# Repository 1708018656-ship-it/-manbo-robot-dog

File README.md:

# 曼波机器狗（Manbo Robot Dog）

> 基于 STM32F103C8T6 的低成本桌面四足机器狗：**说口令就走，还会回话、做表情**。精简版整机约 50–75 元（4 个 SG90 舵机 + SU-03T 离线语音 + OLED + 4 节 5 号电池）；完整版另有蓝牙、超声波避障、红外防跌落、电池检测。

**维护者：[@1708018656-ship-it](https://github.com/1708018656-ship-it)** · 基于 [RussellCooper-DJZ/manbo-robot-dog](https://github.com/RussellCooper-DJZ/manbo-robot-dog)（MIT）

本仓库是在原项目基础上的**整体优化版**：修了一批真实 bug，固件全面非阻塞化，新增看门狗、电池检测和舵机校准，并从零设计了一块可直接下单的**扩展底板 V2**。逐条改动见 [OPTIMIZATION_PLAN.md](OPTIMIZATION_PLAN.md)。

## 两种版本

| | 精简版（推荐入门，省钱） | 完整版 |
|---|---|---|
| 功能 | 语音口令控制 + 运动 + 语音回复 + OLED 表情 | 以上全部 + 蓝牙 + 超声波避障 + 红外防跌落 + 电池检测 |
| 硬件 | [hardware/lite/](hardware/lite/README.md)：70×54 mm 小板，4 节 5 号电池，SU-03T 语音模块（自带喇叭回话），OLED | [hardware/](hardware/README.md)：100×90 mm 扩展底板 V2，2S 锂电 |
| 固件 | `make LITE=1` | `make V2=1`（或原版飞线 `make`） |
| 大概成本（不含电池、下载器） | 约 50–75 元 | 明显更高（多了语音合成、蓝牙、屏幕、传感器和锂电供电） |

<p align="center"><br><sub>精简版底板（70 × 54 mm，13 个元件）。完整版底板见 <a href="hardware/README.md">hardware/</a></sub></p>

## 这一版改了什么

**修复的 bug（都有对应测试或验证）**
- 超声波避障基本测不到 170 cm 内的障碍物（10 ms 轮询漏掉短回波）→ 直接读中断累计的回波宽度
- 主循环命令分发顺序错误，非阻塞状态机被绕过、每个动作执行两遍
- 高级动作语音变成念拼音字母；长语音被截断且会切坏半个汉字
- 体力为 0 时命令被重放；体力 / 开心值只显示 2 位；语音模块与主控命令编码不一致
- `Time` 变量 volatile 不一致、`speed==0` 除零、`commands.h` 缺头文件、ASR `__dso_handle` 重复定义

**固件改进**
- 主循环里不再有秒级延时：动作、语音、状态播报、红外防跌落、OLED 刷新全部非阻塞
- 独立看门狗（约 1.6 s），急停在任何时候都能立即响应
- 电池电压检测（V2 底板）：低电提醒、过低自动趴下
- 每个舵机可单独微调角度（`Hardware/ServoMath.h` 里的 `SERVO_TRIM_DEG`）
- 全部源码 UTF-8（转换前后二进制逐字节一致），GBK 语音文本用 `\x` 转义
- 新增 GCC 构建（`make`），Keil 工程照常可用；删除死代码后代码段约 22.5 KB / 64 KB

**硬件**：见 [hardware/README.md](hardware/README.md)——双降压分离舵机 / 逻辑供电、防反接、自恢复保险丝、超声波 Echo 分压、红外改到耐 5 V 引脚。

## 快速开始

### 1. 编译固件

| 方式 | 命令 / 操作 |
|---|---|
| Keil MDK 5 | 打开 `Project.uvprojx` 编译。用 V2 底板时在 Options → C/C++ → Define 加 `MANBO_BOARD_V2` |
| GCC | `sudo apt install gcc-arm-none-eabi` 后 `make`（原版接线）、`make V2=1`（V2 底板）或 `make LITE=1`（精简版），产物在 `build/` |
| 烧录 | ST-Link：`make flash`，或 Keil / STM32CubeProgrammer 烧 `build/manbo.hex` |

GitHub Actions 每次推送都会编出三种版本的 `.hex`，可在 Actions 页面直接下载。

### 2. 接线

- **用 V2 底板**：模块直接插，见 [hardware/kicad/pinmap.md](hardware/kicad/pinmap.md)
- **原版飞线**：

| 功能 | 引脚 |
|---|---|
| 舵机 1–4（TIM3 CH1–4） | PA6、PA7、PB0、PB1 |
| 蓝牙 HC-05（USART1） | PA9 → 模块 RXD，PA10 ← 模块 TXD |
| SYN6288（USART2） | PA2 → 模块 RXD，PA3 ← 模块 TXD |
| 语音识别（USART3） | PB10 → 模块 RXD，PB11 ← 模块 TXD |
| OLED（软件 I2C） | PB8 SCL，PB9 SDA |
| HC-SR04 | PA0 Trig，PA1 Echo（**建议加 1k/2k 分压，PA1 不耐 5 V**） |
| 红外 ×4 | 前 PA11、后 PA4、左 PA12、右 PA5（V2：PB12–PB15） |

舵机必须单独供电（5 V ≥ 3 A），不要从 Blue Pill 取电。

### 3. 控制

蓝牙串口助手发单个字符即可，9600 8N1。常用：`f` 前进、`b` 后退、`l`/`r` 转弯、`5` 急停、`d` 跳舞、`o` 打招呼、`p` 趴下睡觉、`Z` 播报状态、`x`/`c` 开关超声波避障、`H`/`h` 开关红外防跌落。完整表格（含体力 / 开心值规则）见 [docs/protocol.md](docs/protocol.md)。

## 仓库结构

```text
User/        应用层：main 主循环、ActionTask 动作状态机、AudioTask 语音、SensorTask 超声波、
             BatteryTask 电池、PetStats 体力/开心值、BoardConfig 板型引脚、Watchdog
Hardware/    驱动：Servo/ServoMath、PWM、OLED、syn6288、Hongwai 红外、UltrasonicWave、Timer
System/      Timebase 1 ms 时基、usart1–3（环形缓冲）、Delay、GbkText
Library/ Start/   ST 标准外设库与 CMSIS（Keil 启动文件）
gcc/         GCC 链接脚本与启动文件；Makefile 在根目录
ASRPro_Code/ ESP32 + ASR PRO 语音识别子项目（PlatformIO）
hardware/    扩展底板 V2：生成脚本、KiCad 工程、BOM、Gerber
tests/host/  主机单元测试（无需开发板）：bash tests/host/run_tests.sh
tools/       编码转换、Cortex-M3 语法检查等脚本
docs/        协议、设计方案、审查报告
```

## 测试

```bash
bash tests/host/run_tests.sh          # 状态机、协议覆盖、GBK 截断、体力规则、电池、超声波、舵机换算
bash tools/check_firmware_syntax.sh   # 用 clang 对 Keil 工程全部 C 文件做 Cortex-M3 检查
python3 hardware/gen/build.py --check # 重新生成底板并跑 ERC/DRC，确认提交的文件是最新的
# CI 另外用 KiCad 8 的 kicad-cli 做官方 ERC/DRC
```

## 文档

| 文档 | 说明 |
|---|---|
| [docs/protocol.md](docs/protocol.md) | 串口命令协议（STM32 与语音模块共用的唯一权威表） |
| [hardware/lite/README.md](hardware/lite/README.md) | **精简版**：底板、供电、组装 |
| [docs/su03t.md](docs/su03t.md) | 精简版 SU-03T 口令配置表 |
| [hardware/README.md](hardware/README.md) | 完整版扩展底板：下单、焊接、上电检查 |
| [hardware/采购清单.md](hardware/采购清单.md) | 整机采购清单（板子、模块、舵机、电池） |
| [OPTIMIZATION_PLAN.md](OPTIMIZATION_PLAN.md) | 本次优化的全部改动与原因 |
| [docs/non_blocking_state_machine.md](docs/non_blocking_state_machine.md) | 非阻塞状态机设计 |
| [ASRPro_Code/README.md](ASRPro_Code/README.md) | 语音识别子项目 |

`docs/` 里 `hardware.md`、`hardware-interface.md`、`gait-control.md`、`software.md`、`code_examples.md` 和两篇论文是早期资料，描述的是 8/12 舵机或 STM32F407 的扩展设想，**与当前代码不一致**，仅供参考。

## 已知限制

- 固件改动已通过主机测试和 Cortex-M3 编译检查，**尚未在实物上回归测试**；如发现动作异常，可用 `git log` 定位并反馈。
- V2 底板是脚本生成并自动布线的，已过 KiCad 8 官方 ERC/DRC，**尚未打样**。
- 4 舵机每条腿只有 1 个自由度，步态以趣味动作为主，不追求真实四足运动学。

## 许可证与致谢

MIT 许可证，见 [LICENSE](LICENSE)。原始项目作者 RussellCooper-DJZ；本版由 [@1708018656-ship-it](https://github.com/1708018656-ship-it) 维护和优化，保留原作者版权声明。

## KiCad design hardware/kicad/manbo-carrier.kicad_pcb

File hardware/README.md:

# 曼波机器狗扩展底板 V2

原项目只有飞线接法，没有任何原理图和 PCB。这块底板把 Blue Pill（STM32F103C8T6）、4 个舵机、所有模块和电源集成到一块 100 × 90 mm 的双层板上，同时解决了原接法的几个硬件问题。

> ⚠️ 这块板是用脚本生成并自动布线的，已通过脚本自带的 ERC/DRC，以及 **KiCad 8 官方 ERC/DRC（0 违规、0 未连接，CI 每次推送自动跑）**，**但还没有打样、焊接或实测过**。第一次打样建议先少量（5 片），按下面的「上电检查」一步一步来。

## 和原版接线相比修了什么

| 问题 | 原接法 | V2 底板 |
|---|---|---|
| 舵机一起动 MCU 就复位 | 舵机和逻辑共用一路 5 V | 舵机和逻辑**各用一个降压模块**，舵机轨加 1000 µF |
| HC-SR04 Echo 5 V 接 PA1 | PA1 **不耐 5 V**，长期可能损坏芯片 | 1k/2k 分压到 3.33 V |
| 红外占用 PA11/PA12 | 这是 USB D-/D+，Blue Pill 板载上拉会干扰读数 | 改到 PB12–PB15（耐 5 V） |
| 没有电池电压检测 | ADC 引脚全被占用 | VBAT 经 100k/33k 分压接 PA4，低电提醒 + 自动趴下 |
| 电池接反直接烧 | 无保护 | Q2 P-MOS 防反接 + 3 A 自恢复保险丝 |
| 开关承受全部电流 | 小拨动开关只能过 0.5 A | 开关只控制 Q1 栅极，大电流走 MOS 管 |

## 文件

| 路径 | 内容 |
|---|---|
| `fab/manbo-carrier-gerbers.zip` | **直接上传到嘉立创/JLCPCB 等下单** |
| `kicad/manbo-carrier.kicad_pro` | KiCad 8 工程（原理图 + PCB，可继续修改） |
| `kicad/bom.csv` | 板上元件清单（位号、封装，自动生成） |
| `采购清单.md` | **整机采购清单**（含舵机、模块、电池等） |
| `kicad/pinmap.md` | Blue Pill 每个引脚接到哪里 |
| `kicad/schematic-preview.svg` | 原理图预览（手机也能看） |
| `kicad/drc-report.txt` | 布线和 DRC 结果 |
| `gen/` | 生成脚本：**改设计请改 `gen/design.py` / `gen/layout.py`**，然后运行 `python3 hardware/gen/build.py` |

## 下单参数

层数 2，板厚 1.6 mm，尺寸 100 × 90 mm，最小线宽 0.254 mm（10 mil）、最小间距 0.2 mm，过孔 0.5 mm 孔 / 1.0 mm 焊盘，铜厚 1 oz，阻焊颜色随意。这些都在嘉立创 EDA 的默认规则以内，导入后 DRC 不需要改规则。这些都是常规工艺，打样通常最便宜那档就够。

## 焊接顺序

1. 贴片：Q1、Q2（SOIC-8，注意 1 脚圆点）、F1、电阻电容、LED（绿点/竖线 = 负极，对应丝印 1 脚）
2. 直插：排针/排母、XH 座、电解电容（**长脚 = 正极 = 方焊盘**）
3. Blue Pill 用两条 1×20 **排母**插装，方便更换
4. 降压模块：用排针立在板上，或用短线接到 IN+/IN-/OUT+/OUT- 四个大孔

## 上电检查（第一次一定要按顺序）

1. **先不插 Blue Pill、不接舵机和模块。**
2. 接电池（或 7–8 V 限流电源，限流 0.5 A），J15 接上开关并打开，电源灯亮。
3. **把两个降压模块都调到 5.0 V 再往下走**——MP1584 这类可调模块出厂电压是随机的，直接接可能把 Blue Pill 和舵机烧掉。
4. 用万用表确认：`+5V_SERVO` 和 `+5V` 都是 5.0 V，Blue Pill 排母的 3V3 脚此时为 0（Blue Pill 没插）。
5. 关电，插上 Blue Pill，开电：3V3 脚应为 3.3 V。
6. 烧录 **V2 固件**：`make V2=1`，或在 Keil 里 Options → C/C++ → Define 加上 `MANBO_BOARD_V2`。原版固件引脚不同，红外和电池检测会不工作。
7. 再依次接 OLED、舵机、蓝牙等模块。

## 注意

- **Blue Pill 的 USB 口和电池不要同时供电**：Blue Pill 的 USB 5 V 和 5V 引脚之间多数没有二极管，会互相倒灌。烧录用 SWD（ST-Link）最方便。
- OLED 有两种引脚顺序（GND-VCC 和 VCC-GND），插之前看一眼模块丝印。
- HC-05 是 6 针，HC-06 是 4 针（插在 J6 的 2–5 脚）。模块方向以丝印 `VCC GND TXD RXD` 为准。
- SYN6288 和 ASR PRO 模块的引脚顺序各家不一样，用杜邦线按丝印 `VCC GND RXD TXD` 接（RXD/TXD 是模块自己的引脚名）。
- GND 铺铜：Gerber 里已经带了铺铜。在 KiCad 里打开 PCB 后，如果要改板，先按 **B**（填充全部覆铜）再出图。
- 引脚表以常见 Blue Pill 为准（左排 PB12…3V3，右排 GND…VBAT）。个别山寨板丝印不同，焊之前用 `kicad/pinmap.md` 对照一下。

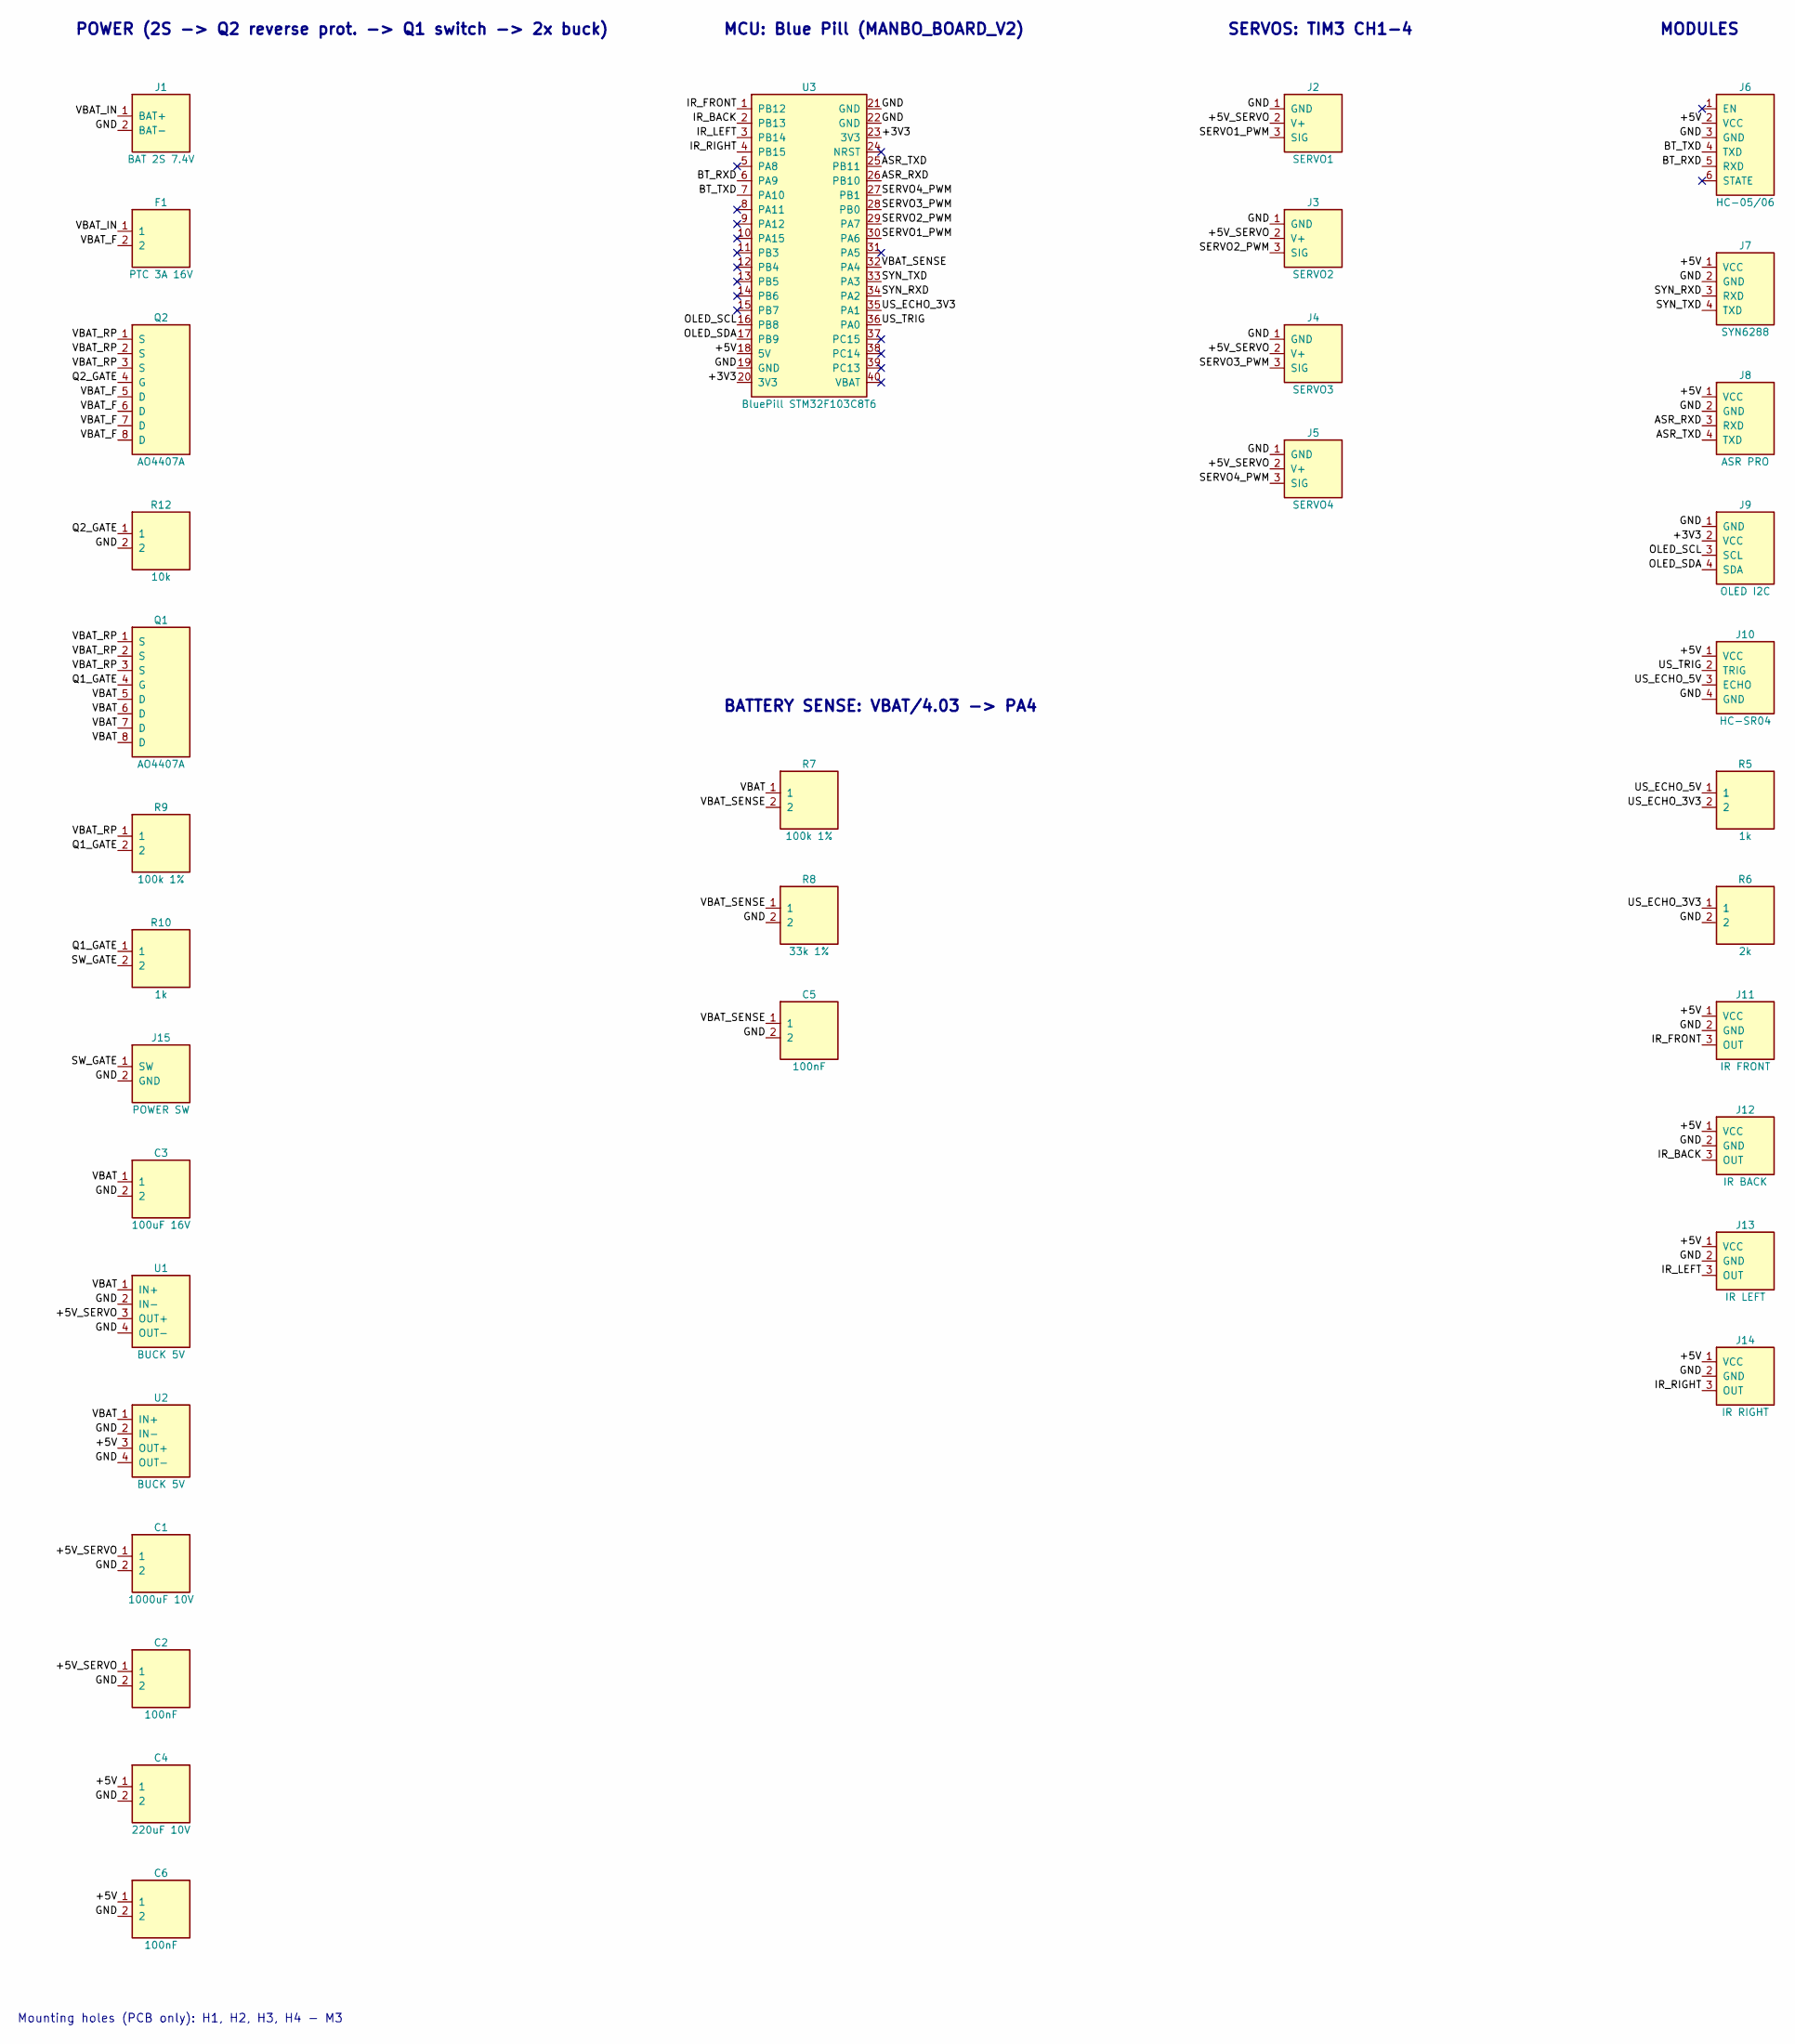
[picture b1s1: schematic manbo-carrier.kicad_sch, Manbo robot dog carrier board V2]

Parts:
C1: 1000uF 10V; CP_Radial_D10.0mm_P5.00mm; LCSC 1000uF 10V 10x13
C2, C5, C6: 100nF; C_0805_2012Metric; LCSC 0805 100nF
C3: 100uF 16V; CP_Radial_D6.3mm_P2.50mm; LCSC 100uF 16V 6.3x7
C4: 220uF 10V; CP_Radial_D6.3mm_P2.50mm; LCSC 220uF 10V 6.3x7
F1: PTC 3A 16V; Fuse_2920_7451Metric; LCSC SMD2920P300TF/24
J1: BAT 2S 7.4V; JST_XH_B2B-XH-A_1x02_P2.50mm_Vertical; LCSC XH2.54 2P
J2: SERVO1; PinHeader_1x03_P2.54mm_Vertical; LCSC 2.54mm header 3P
J3: SERVO2; PinHeader_1x03_P2.54mm_Vertical; LCSC 2.54mm header 3P
J4: SERVO3; PinHeader_1x03_P2.54mm_Vertical; LCSC 2.54mm header 3P
J5: SERVO4; PinHeader_1x03_P2.54mm_Vertical; LCSC 2.54mm header 3P
J6: HC-05/06; PinHeader_1x06_P2.54mm_Vertical; LCSC 2.54mm header 6P
J7: SYN6288; PinHeader_1x04_P2.54mm_Vertical; LCSC 2.54mm header 4P
J8: ASR PRO; PinHeader_1x04_P2.54mm_Vertical; LCSC 2.54mm header 4P
J9: OLED I2C; PinHeader_1x04_P2.54mm_Vertical; LCSC 2.54mm header 4P
J10: HC-SR04; PinHeader_1x04_P2.54mm_Vertical; LCSC 2.54mm header 4P
J11: IR FRONT; PinHeader_1x03_P2.54mm_Vertical; LCSC 2.54mm header 3P
J12: IR BACK; PinHeader_1x03_P2.54mm_Vertical; LCSC 2.54mm header 3P
J13: IR LEFT; PinHeader_1x03_P2.54mm_Vertical; LCSC 2.54mm header 3P
J14: IR RIGHT; PinHeader_1x03_P2.54mm_Vertical; LCSC 2.54mm header 3P
J15: POWER SW; JST_XH_B2B-XH-A_1x02_P2.50mm_Vertical; LCSC XH2.54 2P
Q1, Q2: AO4407A; SOIC-8_3.9x4.9mm_P1.27mm; LCSC AO4407A
R5, R10: 1k; R_0805_2012Metric; LCSC 0805 1k
R6: 2k; R_0805_2012Metric; LCSC 0805 2k
R7, R9: 100k 1%; R_0805_2012Metric; LCSC 0805 100k 1%
R8: 33k 1%; R_0805_2012Metric; LCSC 0805 33k 1%
R12: 10k; R_0805_2012Metric; LCSC 0805 10k
U1, U2: BUCK 5V; BuckModule_2x2_P2.54mm_17.78mm; LCSC MP1584 / Mini560 module
U3: BluePill STM32F103C8T6; BluePill_Socket_2x20_W15.24mm; LCSC Blue Pill STM32F103C8T6

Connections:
+3V3: J9.2 (VCC), U3.20 (3V3), U3.23 (3V3)
+5V: C4.1, C6.1, J6.2 (VCC), J7.1 (VCC), J8.1 (VCC), J10.1 (VCC), J11.1 (VCC), J12.1 (VCC), J13.1 (VCC), J14.1 (VCC), U2.3 (OUT+), U3.18 (5V)
+5V_SERVO: C1.1, C2.1, J2.2 (V+), J3.2 (V+), J4.2 (V+), J5.2 (V+), U1.3 (OUT+)
ASR_RXD: J8.3 (RXD), U3.26 (PB10)
ASR_TXD: J8.4 (TXD), U3.25 (PB11)
BT_RXD: J6.5 (RXD), U3.6 (PA9)
BT_TXD: J6.4 (TXD), U3.7 (PA10)
GND: C1.2, C2.2, C3.2, C4.2, C5.2, C6.2, J1.2 (BAT-), J2.1 (GND), J3.1 (GND), J4.1 (GND), J5.1 (GND), J6.3 (GND), J7.2 (GND), J8.2 (GND), J9.1 (GND), J10.4 (GND), J11.2 (GND), J12.2 (GND), J13.2 (GND), J14.2 (GND), J15.2 (GND), R6.2, R8.2, R12.2, U1.2 (IN-), U1.4 (OUT-), U2.2 (IN-), U2.4 (OUT-), U3.19 (GND), U3.21 (GND), U3.22 (GND)
IR_BACK: J12.3 (OUT), U3.2 (PB13)
IR_FRONT: J11.3 (OUT), U3.1 (PB12)
IR_LEFT: J13.3 (OUT), U3.3 (PB14)
IR_RIGHT: J14.3 (OUT), U3.4 (PB15)
OLED_SCL: J9.3 (SCL), U3.16 (PB8)
OLED_SDA: J9.4 (SDA), U3.17 (PB9)
Q1_GATE: Q1.4 (G), R9.2, R10.1
Q2_GATE: Q2.4 (G), R12.1
SERVO1_PWM: J2.3 (SIG), U3.30 (PA6)
SERVO2_PWM: J3.3 (SIG), U3.29 (PA7)
SERVO3_PWM: J4.3 (SIG), U3.28 (PB0)
SERVO4_PWM: J5.3 (SIG), U3.27 (PB1)
SW_GATE: J15.1 (SW), R10.2
SYN_RXD: J7.3 (RXD), U3.34 (PA2)
SYN_TXD: J7.4 (TXD), U3.33 (PA3)
US_ECHO_3V3: R5.2, R6.1, U3.35 (PA1)
US_ECHO_5V: J10.3 (ECHO), R5.1
US_TRIG: J10.2 (TRIG), U3.36 (PA0)
VBAT: C3.1, Q1.5 (D), Q1.6 (D), Q1.7 (D), Q1.8 (D), R7.1, U1.1 (IN+), U2.1 (IN+)
VBAT_F: F1.2, Q2.5 (D), Q2.6 (D), Q2.7 (D), Q2.8 (D)
VBAT_IN: F1.1, J1.1 (BAT+)
VBAT_RP: Q1.1 (S), Q1.2 (S), Q1.3 (S), Q2.1 (S), Q2.2 (S), Q2.3 (S), R9.1
VBAT_SENSE: C5.1, R7.2, R8.1, U3.32 (PA4)

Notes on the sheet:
POWER (2S -> Q2 reverse prot. -> Q1 switch -> 2x buck)
MCU: Blue Pill (MANBO_BOARD_V2)
SERVOS: TIM3 CH1-4
MODULES
BATTERY SENSE: VBAT/4.03 -> PA4
Mounting holes (PCB only): H1, H2, H3, H4 - M3

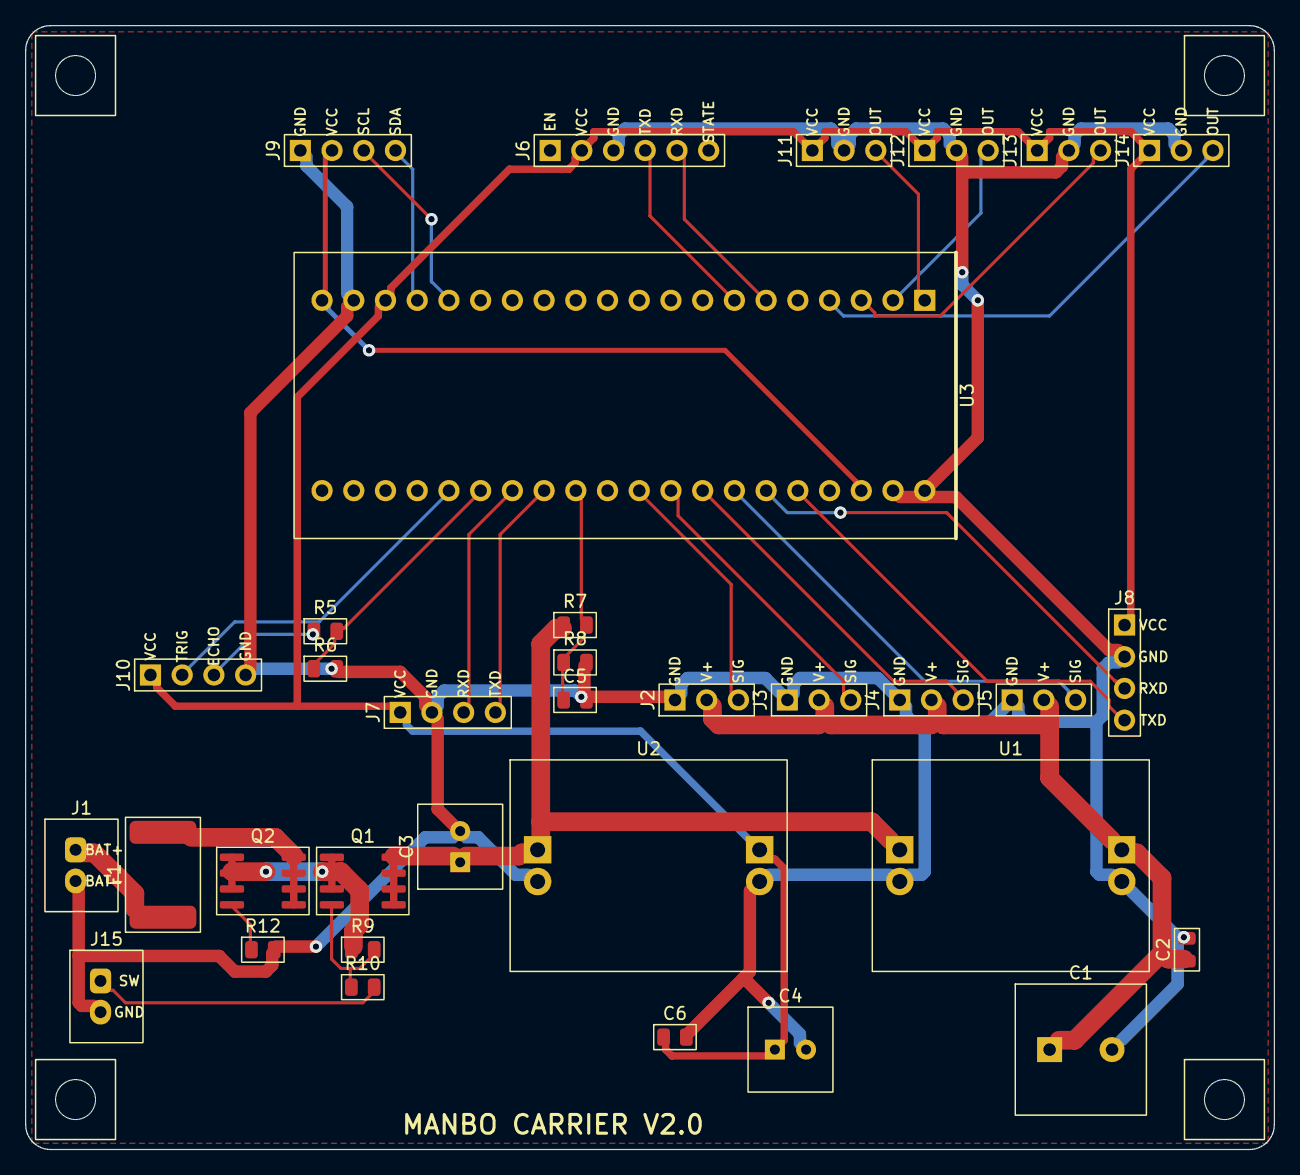
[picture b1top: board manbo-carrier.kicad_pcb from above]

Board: 2 copper layers, 100.0 x 90.0 mm, 38 parts (0 on the bottom side), 31 nets.

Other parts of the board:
H1, H2, H3, H4: M3; MountingHole_3.2mm_M3

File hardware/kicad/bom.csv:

Qty,References,Value,Footprint,Search keyword (LCSC/Taobao),Notes
1,C1,1000uF 10V,CP_Radial_D10.0mm_P5.00mm,1000uF 10V 10x13,
3,C2 C5 C6,100nF,C_0805_2012Metric,0805 100nF,
1,C3,100uF 16V,CP_Radial_D6.3mm_P2.50mm,100uF 16V 6.3x7,
1,C4,220uF 10V,CP_Radial_D6.3mm_P2.50mm,220uF 10V 6.3x7,
1,F1,PTC 3A 16V,Fuse_2920_7451Metric,SMD2920P300TF/24,"Resettable fuse, 3 A hold, >=16 V (servo stall protection)"
4,H1 H2 H3 H4,M3,MountingHole_3.2mm_M3,,M3 mounting hole
1,J1,BAT 2S 7.4V,JST_XH_B2B-XH-A_1x02_P2.50mm_Vertical,XH2.54 2P,2S Li-ion/LiPo input (6.4-8.4 V)
1,J2,SERVO1,PinHeader_1x03_P2.54mm_Vertical,2.54mm header 3P,"SG90 servo 1 (brown=GND, red=V+, orange=SIG)"
1,J3,SERVO2,PinHeader_1x03_P2.54mm_Vertical,2.54mm header 3P,"SG90 servo 2 (brown=GND, red=V+, orange=SIG)"
1,J4,SERVO3,PinHeader_1x03_P2.54mm_Vertical,2.54mm header 3P,"SG90 servo 3 (brown=GND, red=V+, orange=SIG)"
1,J5,SERVO4,PinHeader_1x03_P2.54mm_Vertical,2.54mm header 3P,"SG90 servo 4 (brown=GND, red=V+, orange=SIG)"
1,J6,HC-05/06,PinHeader_1x06_P2.54mm_Vertical,2.54mm header 6P,Bluetooth module socket (HC-05 6-pin; HC-06 4-pin plugs into pins 2-5)
1,J7,SYN6288,PinHeader_1x04_P2.54mm_Vertical,2.54mm header 4P,SYN6288 speech synthesis module
1,J8,ASR PRO,PinHeader_1x04_P2.54mm_Vertical,2.54mm header 4P,ASR PRO voice recognition module
1,J9,OLED I2C,PinHeader_1x04_P2.54mm_Vertical,2.54mm header 4P,0.96in SSD1306 I2C OLED (plugs in directly)
1,J10,HC-SR04,PinHeader_1x04_P2.54mm_Vertical,2.54mm header 4P,Ultrasonic sensor (plugs in directly)
1,J11,IR FRONT,PinHeader_1x03_P2.54mm_Vertical,2.54mm header 3P,"IR cliff sensor front (FC-51 style, VCC GND OUT)"
1,J12,IR BACK,PinHeader_1x03_P2.54mm_Vertical,2.54mm header 3P,"IR cliff sensor back (FC-51 style, VCC GND OUT)"
1,J13,IR LEFT,PinHeader_1x03_P2.54mm_Vertical,2.54mm header 3P,"IR cliff sensor left (FC-51 style, VCC GND OUT)"
1,J14,IR RIGHT,PinHeader_1x03_P2.54mm_Vertical,2.54mm header 3P,"IR cliff sensor right (FC-51 style, VCC GND OUT)"
1,J15,POWER SW,JST_XH_B2B-XH-A_1x02_P2.50mm_Vertical,XH2.54 2P,"External ON/OFF switch (signal level, any small switch)"
1,Q1,AO4407A,SOIC-8_3.9x4.9mm_P1.27mm,AO4407A,"P-MOSFET -30V -12A, power switch"
1,Q2,AO4407A,SOIC-8_3.9x4.9mm_P1.27mm,AO4407A,"P-MOSFET -30V -12A, reverse-polarity protection"
1,R6,2k,R_0805_2012Metric,0805 2k,
1,R8,33k 1%,R_0805_2012Metric,0805 33k 1%,
2,R7 R9,100k 1%,R_0805_2012Metric,0805 100k 1%,
2,R5 R10,1k,R_0805_2012Metric,0805 1k,
1,R12,10k,R_0805_2012Metric,0805 10k,
1,U1,BUCK 5V,BuckModule_2x2_P2.54mm_17.78mm,MP1584 / Mini560 module,"DC-DC buck module, servo rail, >=3 A (e.g. Mini560 5V / MP1584)"
1,U2,BUCK 5V,BuckModule_2x2_P2.54mm_17.78mm,MP1584 / Mini560 module,"DC-DC buck module, logic rail, >=1 A (e.g. MP1584 / Mini360 set to 5.0 V)"
1,U3,BluePill STM32F103C8T6,BluePill_Socket_2x20_W15.24mm,Blue Pill STM32F103C8T6,Blue Pill on 2x 1x20 female headers

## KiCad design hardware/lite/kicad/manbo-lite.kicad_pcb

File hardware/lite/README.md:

# 曼波机器狗 精简版（LITE）

**听懂口令、走起来、开口回话、屏幕做表情**。语音合成模块、蓝牙、超声波、红外、电池检测全部去掉，换成最便宜的方案。

## 和完整版的区别

| | 完整版 V2 | 精简版 |
|---|---|---|
| 控制 | 蓝牙 + 语音识别（ASR PRO） | **语音口令（SU-03T）** |
| 语音回复 | SYN6288（约 50 元） | **SU-03T 自带喇叭**：识别后自动回话，开机/自动停下时由单片机触发播报 |
| 屏幕表情 | 有 | **有**（0.96 寸 OLED，直接插 J7） |
| 超声波 / 红外 / 电池检测 | 有 | 无 |
| 供电 | 2S 锂电 + 平衡充 + 两个降压模块 + MOS 管 | **4 节 5 号电池盒（带开关）** + 两个二极管 |
| 底板 | 100 × 90 mm，34 个元件 | **70 × 54 mm，13 个元件** |
| 固件 | `make` / `make V2=1` | **`make LITE=1`**（Keil 里加 `MANBO_LITE`） |

## 电源为什么这样设计

- **D1 SS34**：防电池接反；同时把新碱性电池的 6.4 V 降到约 6 V，不超过 SG90 的 6 V 上限。
- **D2 M7（1N4007）**：给 Blue Pill 和语音模块单独供电，再降约 0.8 V，让新碱性电池也不超过 SU-03T 的 5.5 V 上限。
- **C2 470 µF**：舵机启动时电池电压会被拉低，D2 + C2 让单片机和语音模块撑过这一下，不会复位。
- **电池**：碱性和镍氢充电电池都能用。镍氢（1.2 V × 4）更耐用；电池快没电时语音模块会先停止响应，这就是该换电池的信号。

## 文件

| 路径 | 内容 |
|---|---|
| `fab/manbo-lite-gerbers.zip` | 直接上传嘉立创下单 |
| `kicad/` | KiCad 8 工程、BOM、引脚表、预览图 |
| [采购清单.md](采购清单.md) | 整机要买的东西 |
| [../../docs/su03t.md](../../docs/su03t.md) | **SU-03T 口令配置表（必看）** |

## 组装和上电

1. 焊 D1、D2（注意二极管有竖线的一端 = 负极，对准丝印竖线）、C3，再焊排针排母、电解电容（长脚正极 = 方焊盘）。
2. **先不插 Blue Pill**，装电池打开开关，量 Blue Pill 排母的 5V 脚：应该在 3.6–5.5 V 之间。
3. 插 Blue Pill，烧录 `make LITE=1` 编出的固件（或 GitHub Actions 里 `manbo-firmware-lite` 的 `.hex`）。
4. 按 [docs/su03t.md](../../docs/su03t.md) 配置好 SU-03T（含「主动播报」三条），插到 J6；OLED 插到 J7（注意 GND-VCC 顺序）；再接舵机。
5. 开机应听到"小呆来啦"、屏幕出现表情。说"小呆小呆，前进"。说"停"立即停；没听清的话 10 秒后会说"走累了"并自己停。

> 不想打板：这块板电路很简单，用一块洞洞板（约 1 元）照着 `kicad/pinmap.md` 飞线也完全可以。

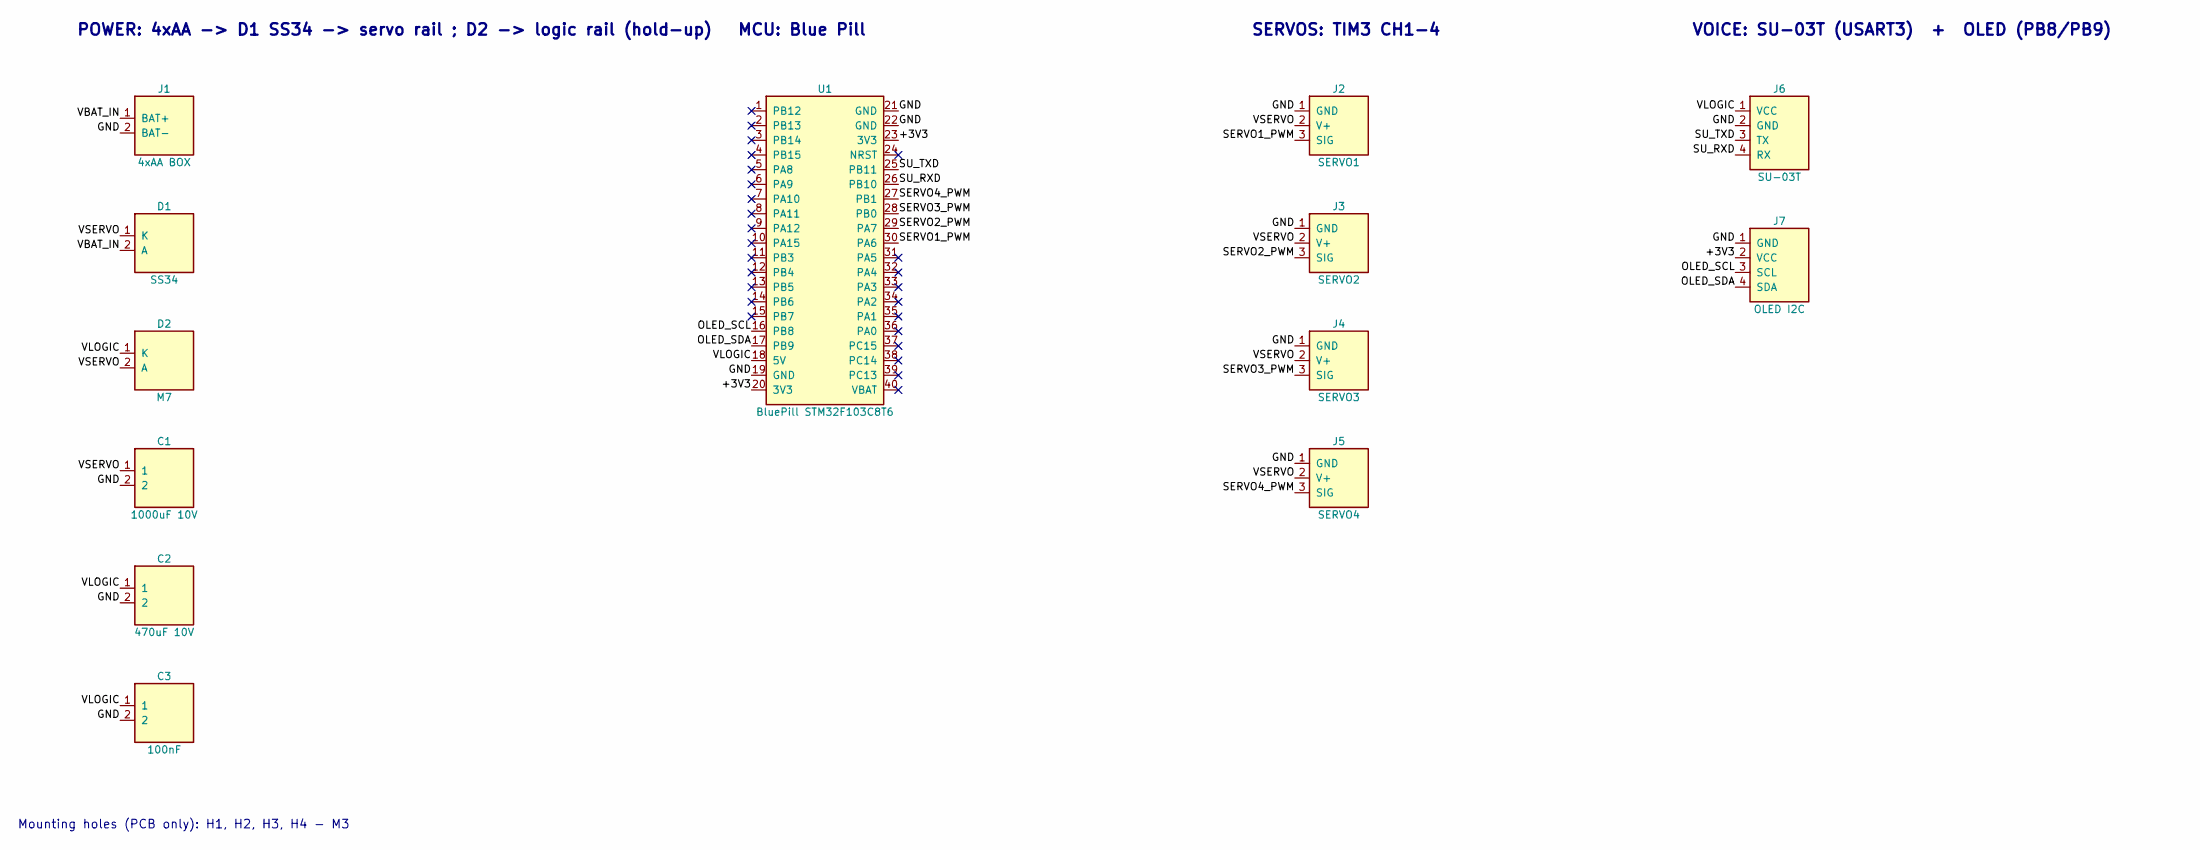
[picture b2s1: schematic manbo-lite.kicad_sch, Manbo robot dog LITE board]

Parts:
C1: 1000uF 10V; CP_Radial_D10.0mm_P5.00mm; LCSC 1000uF 10V 10x13
C2: 470uF 10V; CP_Radial_D8.0mm_P3.50mm; LCSC 470uF 10V 8x12
C3: 100nF; C_0805_2012Metric; LCSC 0805 100nF
D1: SS34; D_SMA; LCSC SS34 SMA
D2: M7; D_SMA; LCSC M7 1N4007 SMA
J1: 4xAA BOX; JST_XH_B2B-XH-A_1x02_P2.50mm_Vertical; LCSC XH2.54 2P
J2: SERVO1; PinHeader_1x03_P2.54mm_Vertical; LCSC 2.54mm header 3P
J3: SERVO2; PinHeader_1x03_P2.54mm_Vertical; LCSC 2.54mm header 3P
J4: SERVO3; PinHeader_1x03_P2.54mm_Vertical; LCSC 2.54mm header 3P
J5: SERVO4; PinHeader_1x03_P2.54mm_Vertical; LCSC 2.54mm header 3P
J6: SU-03T; PinHeader_1x04_P2.54mm_Vertical; LCSC 2.54mm header 4P
J7: OLED I2C; PinHeader_1x04_P2.54mm_Vertical; LCSC 2.54mm header 4P
U1: BluePill STM32F103C8T6; BluePill_Socket_2x20_W15.24mm; LCSC Blue Pill STM32F103C8T6

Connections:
+3V3: J7.2 (VCC), U1.20 (3V3), U1.23 (3V3)
GND: C1.2, C2.2, C3.2, J1.2 (BAT-), J2.1 (GND), J3.1 (GND), J4.1 (GND), J5.1 (GND), J6.2 (GND), J7.1 (GND), U1.19 (GND), U1.21 (GND), U1.22 (GND)
OLED_SCL: J7.3 (SCL), U1.16 (PB8)
OLED_SDA: J7.4 (SDA), U1.17 (PB9)
SERVO1_PWM: J2.3 (SIG), U1.30 (PA6)
SERVO2_PWM: J3.3 (SIG), U1.29 (PA7)
SERVO3_PWM: J4.3 (SIG), U1.28 (PB0)
SERVO4_PWM: J5.3 (SIG), U1.27 (PB1)
SU_RXD: J6.4 (RX), U1.26 (PB10)
SU_TXD: J6.3 (TX), U1.25 (PB11)
VBAT_IN: D1.2 (A), J1.1 (BAT+)
VLOGIC: C2.1, C3.1, D2.1 (K), J6.1 (VCC), U1.18 (5V)
VSERVO: C1.1, D1.1 (K), D2.2 (A), J2.2 (V+), J3.2 (V+), J4.2 (V+), J5.2 (V+)

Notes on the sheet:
POWER: 4xAA -> D1 SS34 -> servo rail ; D2 -> logic rail (hold-up)
MCU: Blue Pill
SERVOS: TIM3 CH1-4
VOICE: SU-03T (USART3) + OLED (PB8/PB9)
Mounting holes (PCB only): H1, H2, H3, H4 - M3

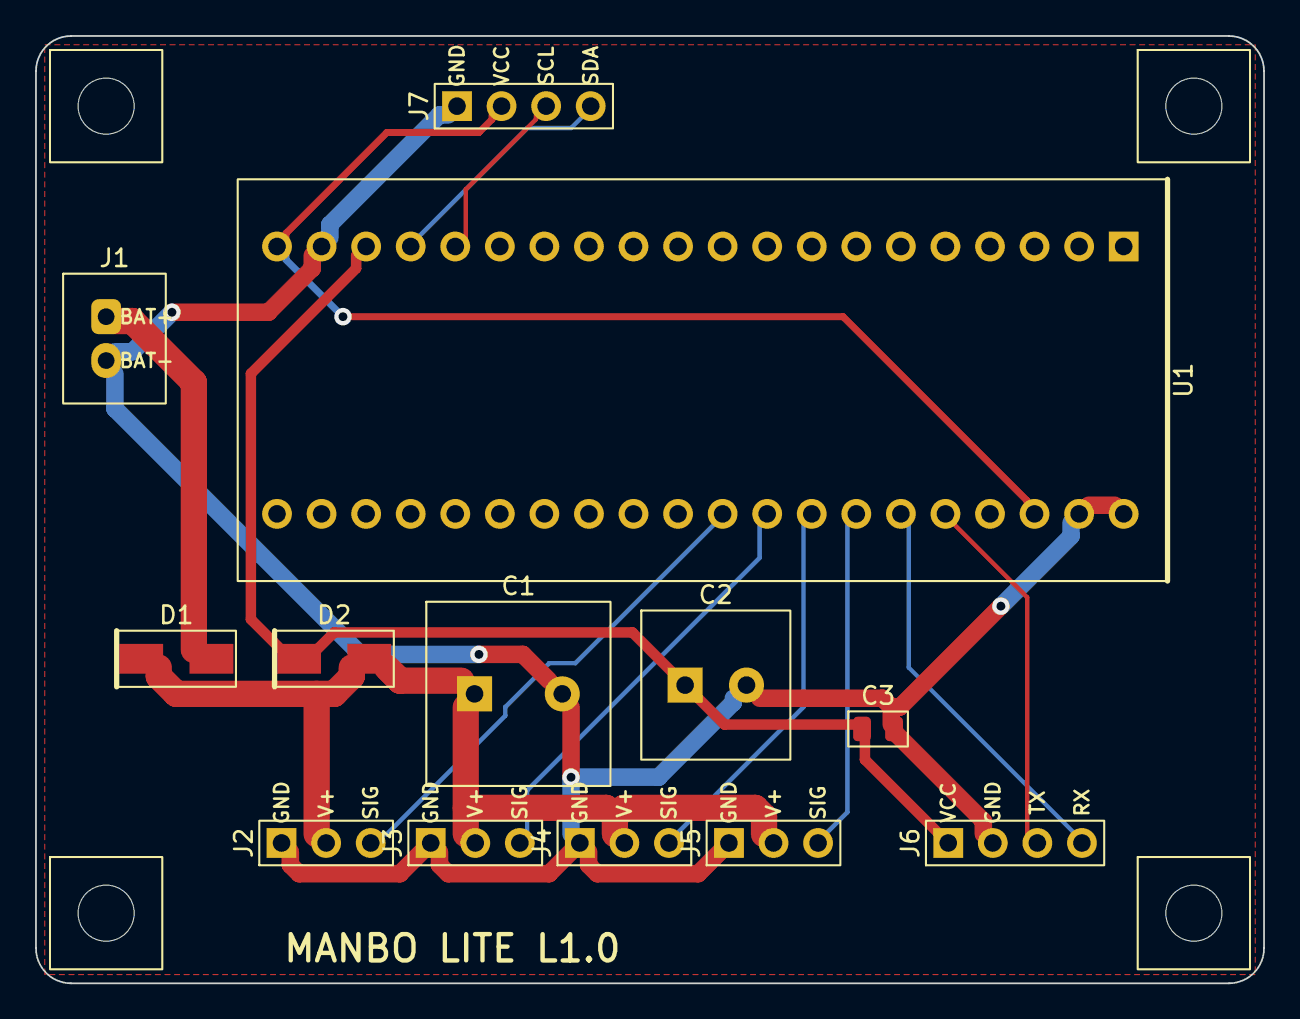
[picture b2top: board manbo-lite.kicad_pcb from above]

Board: 2 copper layers, 70.0 x 54.0 mm, 17 parts (0 on the bottom side), 13 nets.

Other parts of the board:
H1, H2, H3, H4: M3; MountingHole_3.2mm_M3

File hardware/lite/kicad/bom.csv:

Qty,References,Value,Footprint,Search keyword (LCSC/Taobao),Notes
1,C1,1000uF 10V,CP_Radial_D10.0mm_P5.00mm,1000uF 10V 10x13,
1,C2,470uF 10V,CP_Radial_D8.0mm_P3.50mm,470uF 10V 8x12,
1,C3,100nF,C_0805_2012Metric,0805 100nF,
1,D1,SS34,D_SMA,SS34 SMA,Schottky 3 A: reverse-polarity protection for the whole board
1,D2,M7,D_SMA,M7 1N4007 SMA,"1N4007 (M7): logic rail isolation, drops ~0.8 V so fresh alkaline stays below 5.5 V"
4,H1 H2 H3 H4,M3,MountingHole_3.2mm_M3,,M3 mounting hole
1,J1,4xAA BOX,JST_XH_B2B-XH-A_1x02_P2.50mm_Vertical,XH2.54 2P,4xAA battery box with switch (NiMH 4.8 V or alkaline 6 V)
1,J2,SERVO1,PinHeader_1x03_P2.54mm_Vertical,2.54mm header 3P,"SG90 servo 1 (brown=GND, red=V+, orange=SIG)"
1,J3,SERVO2,PinHeader_1x03_P2.54mm_Vertical,2.54mm header 3P,"SG90 servo 2 (brown=GND, red=V+, orange=SIG)"
1,J4,SERVO3,PinHeader_1x03_P2.54mm_Vertical,2.54mm header 3P,"SG90 servo 3 (brown=GND, red=V+, orange=SIG)"
1,J5,SERVO4,PinHeader_1x03_P2.54mm_Vertical,2.54mm header 3P,"SG90 servo 4 (brown=GND, red=V+, orange=SIG)"
1,J6,SU-03T,PinHeader_1x04_P2.54mm_Vertical,2.54mm header 4P,"SU-03T voice module: VCC, GND, TX(B7), RX(B6); mic + speaker plug into the module"
1,J7,OLED I2C,PinHeader_1x04_P2.54mm_Vertical,2.54mm header 4P,"0.96in SSD1306 I2C OLED, powered from the Blue Pill 3V3 (plugs in directly)"
1,U1,BluePill STM32F103C8T6,BluePill_Socket_2x20_W15.24mm,Blue Pill STM32F103C8T6,Blue Pill on 2x 1x20 female headers

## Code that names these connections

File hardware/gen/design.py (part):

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# Left row is pin 1..20 from the USB end, right row 21..40 from the USB end.
# Verify against your own board: a few clones differ in silkscreen only.
# ---------------------------------------------------------------------------
BLUEPILL_LEFT = ["PB12", "PB13", "PB14", "PB15", "PA8", "PA9", "PA10", "PA11",
                 "PA12", "PA15", "PB3", "PB4", "PB5", "PB6", "PB7", "PB8",
                 "PB9", "5V", "GND", "3V3"]
BLUEPILL_RIGHT = ["GND", "GND", "3V3", "NRST", "PB11", "PB10", "PB1", "PB0",
                  "PA7", "PA6", "PA5", "PA4", "PA3", "PA2", "PA1", "PA0",
                  "PC15", "PC14", "PC13", "VBAT"]


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# Worst case: 4x SG90 stall 2.8 A @ 5 V + logic 0.3 A -> ~2.4 A from a 7.4 V pack.
# 1812-size PTCs top out around 2.6-3 A and are often rated only 6-8 V (< 8.4 V
# full 2S), so use a 2920 part rated >= 16 V.
P(two_pin("F1", "PTC 3A 16V", "Fuse:Fuse_2920_7451Metric", "VBAT_IN", "VBAT_F",
          "Resettable fuse, 3 A hold, >=16 V (servo stall protection)", "SMD2920P300TF/24", "power"))
# Q2: reverse-polarity protection. P-MOSFET with Drain on the battery side:
#     body diode conducts first, then Vgs = -VBAT turns the channel on.
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       {"1": "VBAT_RP", "2": "VBAT_RP", "3": "VBAT_RP", "4": "Q2_GATE",
        "5": "VBAT_F", "6": "VBAT_F", "7": "VBAT_F", "8": "VBAT_F"},
       "P-MOSFET -30V -12A, reverse-polarity protection", "AO4407A", group="power"))
P(two_pin("R12", "10k", R0805, "Q2_GATE", "GND", "Q2 gate to GND", "0805 10k", "power"))
# Q1: high-side power switch. Source on the supply side so the body diode
#     cannot leak current to the load while off (a single FET cannot be both
#     the switch and the reverse protection). A small panel switch pulls the
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       {"1": "VBAT_RP", "2": "VBAT_RP", "3": "VBAT_RP", "4": "Q1_GATE",
        "5": "VBAT", "6": "VBAT", "7": "VBAT", "8": "VBAT"},
       "P-MOSFET -30V -12A, power switch", "AO4407A", group="power"))
P(two_pin("R9", "100k 1%", R0805, "VBAT_RP", "Q1_GATE", "Gate pull-up: off when switch open", "0805 100k 1%", "power"))
P(two_pin("R10", "1k", R0805, "Q1_GATE", "SW_GATE", "Gate series resistor", "0805 1k", "power"))
P(header("J15", "POWER SW", ["SW", "GND"], ["SW_GATE", "GND"],
         "External ON/OFF switch (signal level, any small switch)",
         fp="Connector_JST:JST_XH_B2B-XH-A_1x02_P2.50mm_Vertical", group="power"))
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P(two_pin("C6", "100nF", C0805, "+5V", "GND", "Logic rail HF decoupling", "0805 100nF", "power"))
# ------------------------------------------------------------------ MCU ----
BP_NETS = {
    "PB12": "IR_FRONT", "PB13": "IR_BACK", "PB14": "IR_LEFT", "PB15": "IR_RIGHT",
    "PA9": "BT_RXD", "PA10": "BT_TXD",             # USART1 (names from module side)
    "PB8": "OLED_SCL", "PB9": "OLED_SDA",
    "PB10": "ASR_RXD", "PB11": "ASR_TXD",          # USART3
    "PB0": "SERVO3_PWM", "PB1": "SERVO4_PWM",
    "PA6": "SERVO1_PWM", "PA7": "SERVO2_PWM",      # TIM3 CH1..CH4
    "PA4": "VBAT_SENSE",                           # ADC1_IN4
    "PA2": "SYN_RXD", "PA3": "SYN_TXD",            # USART2
    "PA0": "US_TRIG", "PA1": "US_ECHO_3V3",
    "5V": "+5V", "GND": "GND", "3V3": "+3V3",
}
bp_pins, bp_nets = [], {}
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P(header("J10", "HC-SR04", ["VCC", "TRIG", "ECHO", "GND"],
         ["+5V", "US_TRIG", "US_ECHO_5V", "GND"], "Ultrasonic sensor (plugs in directly)",
         group="modules"))
# Echo is a 5 V output; PA1 is NOT 5 V tolerant -> divide to 3.33 V.
P(two_pin("R5", "1k", R0805, "US_ECHO_5V", "US_ECHO_3V3", "Echo level shift (top)", "0805 1k", "modules"))
P(two_pin("R6", "2k", R0805, "US_ECHO_3V3", "GND", "Echo level shift (bottom)", "0805 2k", "modules"))
for i, (ref, side) in enumerate((("J11", "FRONT"), ("J12", "BACK"), ("J13", "LEFT"), ("J14", "RIGHT"))):
    P(header(ref, "IR " + side, ["VCC", "GND", "OUT"], ["+5V", "GND", "IR_" + side],
             "IR cliff sensor %s (FC-51 style, VCC GND OUT)" % side.lower(), group="modules"))

# ------------------------------------------------------- battery sensing ---
P(two_pin("R7", "100k 1%", R0805, "VBAT", "VBAT_SENSE", "VBAT divider top", "0805 100k 1%", "sense"))
P(two_pin("R8", "33k 1%", R0805, "VBAT_SENSE", "GND", "VBAT divider bottom", "0805 33k 1%", "sense"))
P(two_pin("C5", "100nF", C0805, "VBAT_SENSE", "GND", "ADC input filter", "0805 100nF", "sense"))

# --------------------------------------------------------------- mechanics -
for i in range(1, 5):
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

# firmware fixed pins that the board must match (checked by build.py)
FIRMWARE_PINS = {"PA6": "SERVO1_PWM", "PA7": "SERVO2_PWM", "PB0": "SERVO3_PWM", "PB1": "SERVO4_PWM",
                 "PA9": "BT_RXD", "PA10": "BT_TXD", "PA2": "SYN_RXD", "PA3": "SYN_TXD",
                 "PB10": "ASR_RXD", "PB11": "ASR_TXD", "PB8": "OLED_SCL", "PB9": "OLED_SDA",
                 "PA0": "US_TRIG", "PA1": "US_ECHO_3V3"}

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

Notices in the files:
README.md:
License: MIT
